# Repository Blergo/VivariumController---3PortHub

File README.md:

3 port hub that handles termiation for the Vivarium Controller project - For more information please see "VivariumController---Master" Repository.

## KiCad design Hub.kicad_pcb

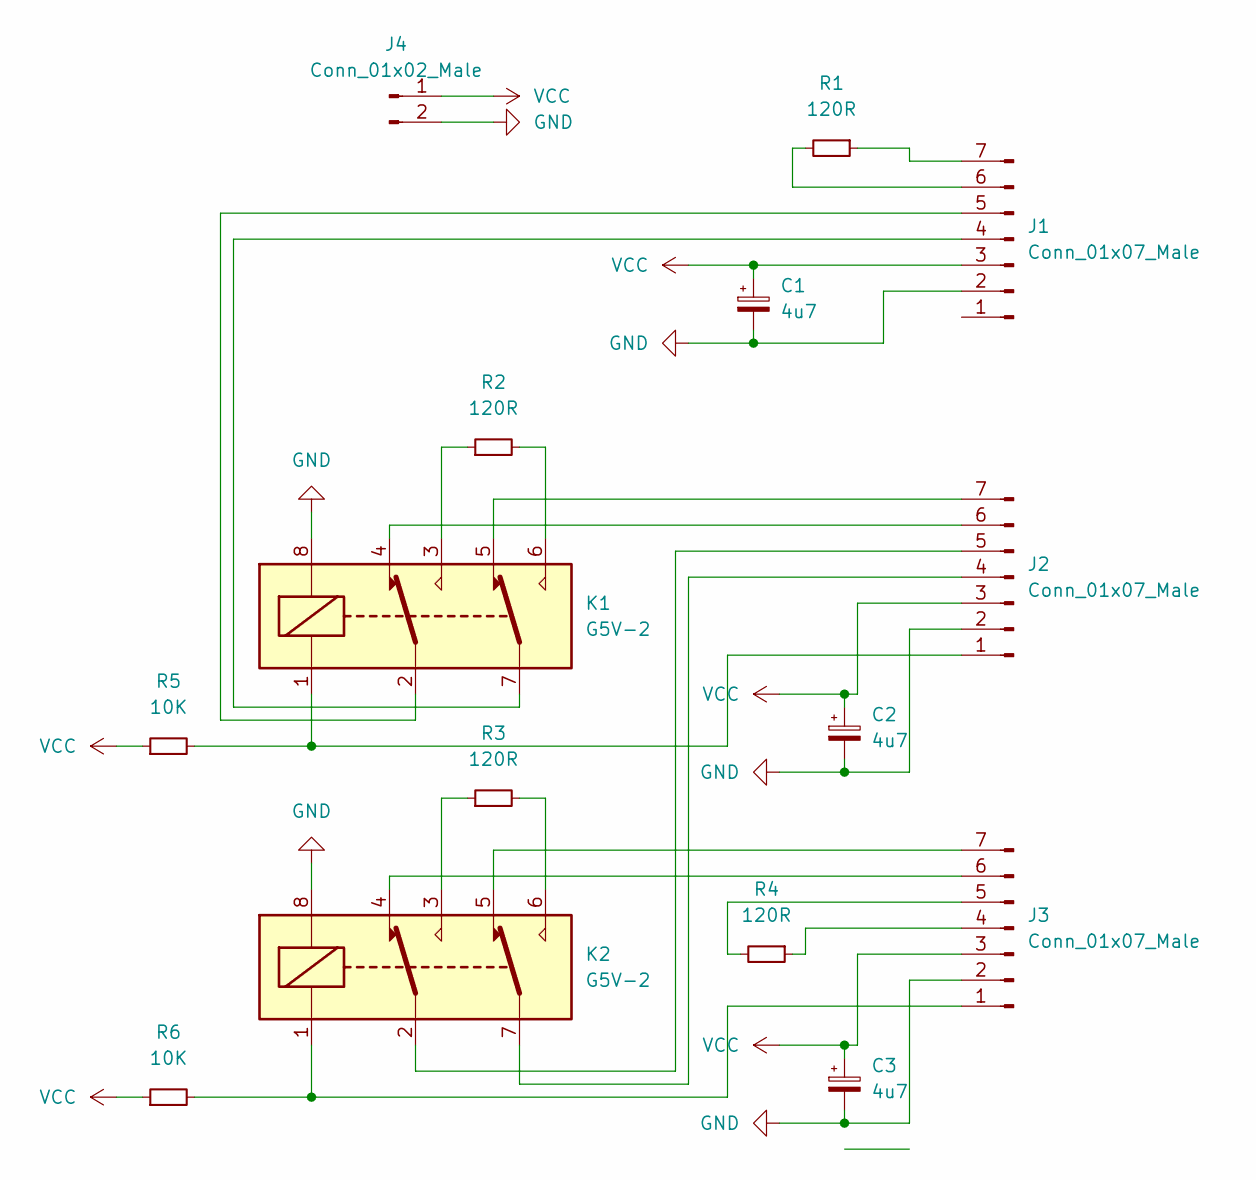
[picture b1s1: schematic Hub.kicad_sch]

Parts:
C1, C2, C3: 4u7; C_Radial_D5.0mm_H11.0mm_P2.00mm
J1, J2, J3: Conn_01x07_Male; PinHeader_1x07_P2.54mm_Vertical
J4: Conn_01x02_Male; PinHeader_1x02_P2.54mm_Vertical
K1, K2: G5V-2; Relay_DPDT_AXICOM_IMSeries_Pitch5.08mm
R1, R2, R3, R4: 120R; R_0805_2012Metric
R5, R6: 10K; R_0805_2012Metric

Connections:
GND: C1.2, C2.2, C3.2, J1.2, J2.2, J3.2, J4.2, K1.8, K2.8
unnamed: J1.4, K1.7
unnamed: J1.5, K1.2
unnamed: J1.6, R1.2
unnamed: J1.7, R1.1
unnamed: J2.1, K1.1, R5.2
unnamed: J2.4, K2.7
unnamed: J2.5, K2.2
unnamed: J2.6, K1.4
unnamed: J2.7, K1.5
unnamed: J3.1, K2.1, R6.2
unnamed: J3.4, R4.1
unnamed: J3.5, R4.2
unnamed: J3.6, K2.4
unnamed: J3.7, K2.5
unnamed: K1.3, R2.1
unnamed: K1.6, R2.2
unnamed: K2.3, R3.1
unnamed: K2.6, R3.2
VCC: C1.1, C2.1, C3.1, J1.3, J2.3, J3.3, J4.1, R5.1, R6.1

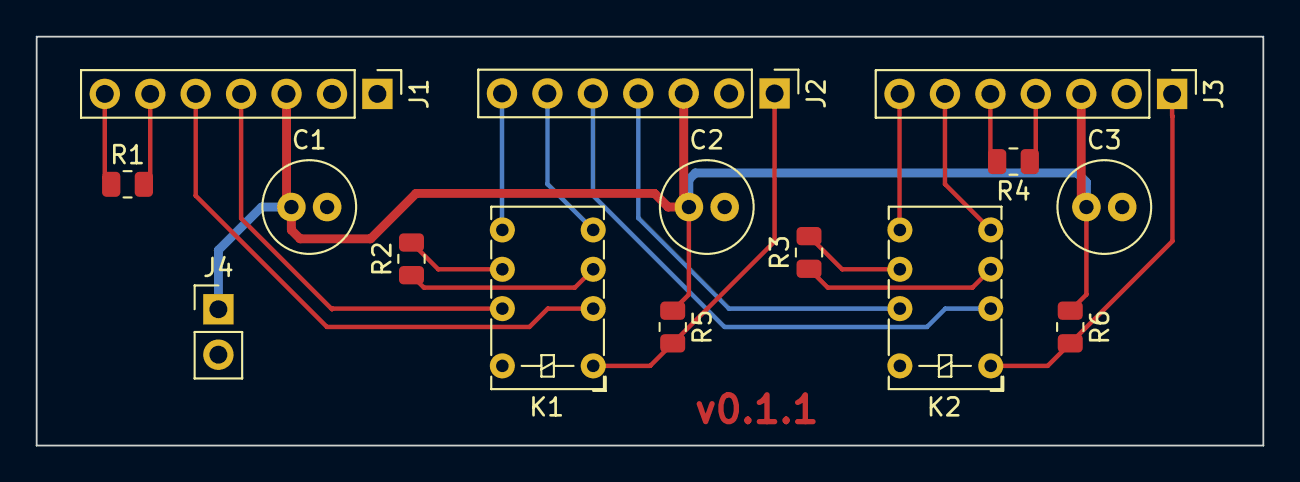
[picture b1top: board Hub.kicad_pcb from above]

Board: 2 copper layers, 68.6 x 22.9 mm, 15 parts (0 on the bottom side), 20 nets.

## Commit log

2022-01-08 v0.1.1alpha
